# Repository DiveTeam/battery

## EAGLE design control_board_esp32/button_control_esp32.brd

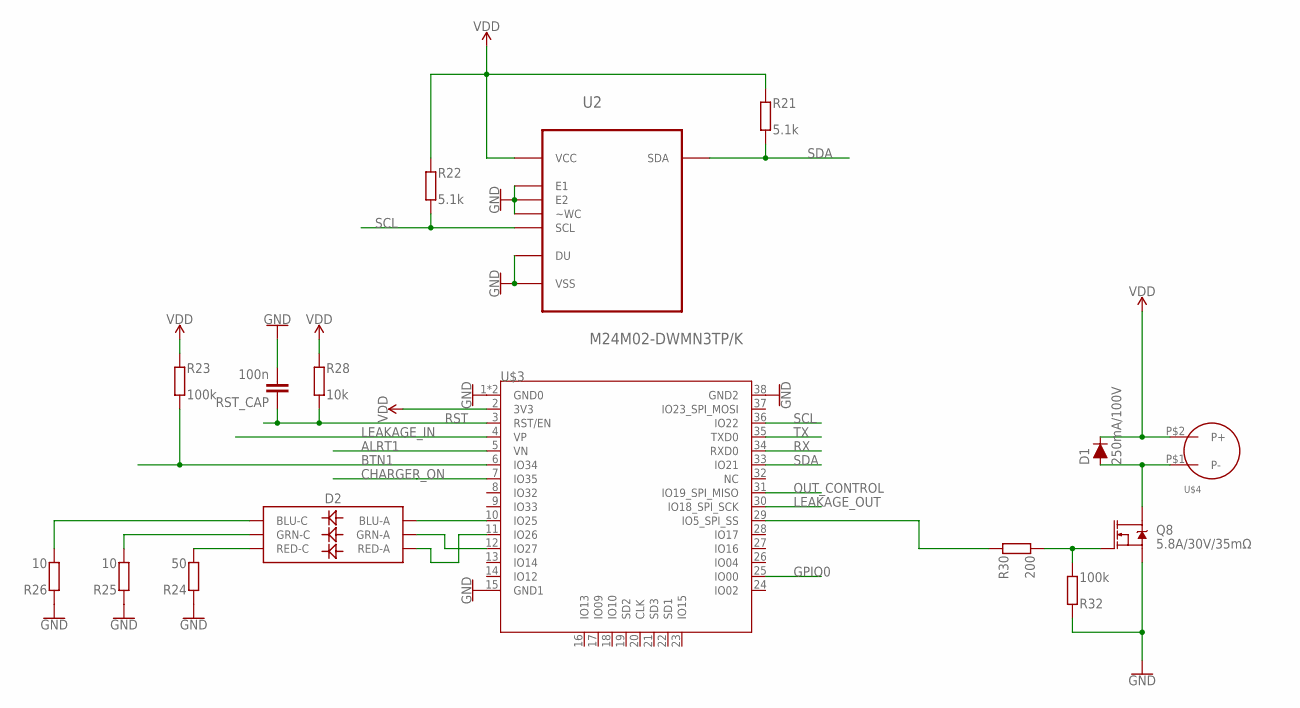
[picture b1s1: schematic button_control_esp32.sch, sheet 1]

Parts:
D1: 250mA/100V; SOD-323
D2: LED-RGBNO_IC; LED-TRICOLOR-5050
Q8: 5.8A/30V/35mΩ; SOT23-3
R21, R22: 5.1k; R0603
R23, R32: 100k; R0603
R24: 50; R0603
R25, R26: 10; R0603
R28: 10k; R0603
R30: 200; R0603
RST_CAP: 100n; C0603
U2: M24M02-DWMN3TP/K; SOIC127P600X175-8N
U$3: ESP32; TTGO_ESP32
U$4: VIBRO

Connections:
ALRT1: U$3.5 (VN); also elsewhere on the board
BTN1: R23.1, U$3.6 (IO34); also elsewhere on the board
CHARGER_ON: U$3.7 (IO35); also elsewhere on the board
GND: Q8.2 (S), R24.2, R25.2, R26.2, R32.2, RST_CAP.2, U2.1 (DU), U2.2 (E1), U2.3 (E2), U2.4 (VSS), U2.7 (~WC), U$3.1 (GND0), U$3.15 (GND1), U$3.38 (GND2), U$3.P$1 (GND0); also elsewhere on the board
GPIO0: U$3.25 (IO00); also elsewhere on the board
LEAKAGE_IN: U$3.4 (VP); also elsewhere on the board
LEAKAGE_OUT: U$3.30 (IO18_SPI_SCK); also elsewhere on the board
unnamed: D2.3 (BLU-A), U$3.10 (IO25)
unnamed: D2.1 (GRN-A), U$3.12 (IO27)
unnamed: D2.2 (RED-A), U$3.11 (IO26)
unnamed: Q8.1 (G), R30.1, R32.1
unnamed: R30.2, U$3.29 (IO5_SPI_SS)
unnamed: D2.4 (BLU-C), R26.1
unnamed: D2.6 (GRN-C), R25.1
unnamed: D2.5 (RED-C), R24.1
unnamed: D1.A, Q8.3 (D), U$4.P$1 (P-)
OUT_CONTROL: U$3.31 (IO19_SPI_MISO); also elsewhere on the board
RST: R28.1, RST_CAP.1, U$3.3 (RST/EN); also elsewhere on the board
RX: U$3.34 (RXD0); also elsewhere on the board
SCL: R22.1, U2.6 (SCL), U$3.36 (IO22); also elsewhere on the board
SDA: R21.1, U2.5 (SDA), U$3.33 (IO21); also elsewhere on the board
TX: U$3.35 (TXD0); also elsewhere on the board
VDD: D1.C, R21.2, R22.2, R23.2, R28.2, U2.8 (VCC), U$3.2 (3V3), U$4.P$2 (P+); also elsewhere on the board

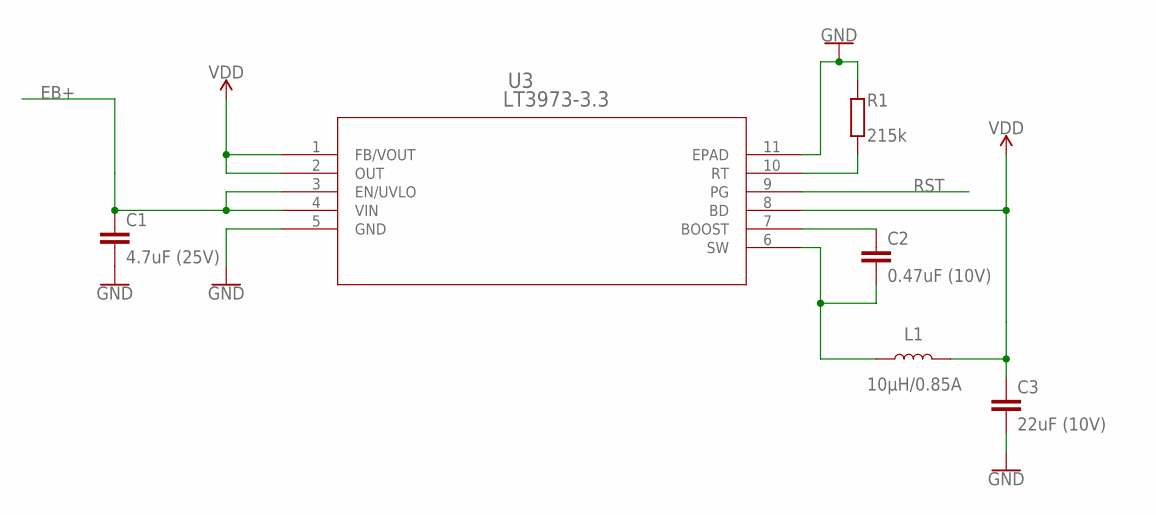
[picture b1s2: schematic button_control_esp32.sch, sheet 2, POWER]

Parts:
C1: 4.7uF (25V); C1206
C2: 0.47uF (10V); C0603K
C3: 22uF (10V); C1206
L1: 10µH/0.85A; INDUCTOR_4.7UH
R1: 215k; R0603
U3: LT3973-3.3; DFN-10_DD

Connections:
BOOST: C2.1, U3.7 (BOOST)
EB+: C1.1, U3.3 (EN/UVLO), U3.4 (VIN); also elsewhere on the board
GND: C1.2, C3.2, R1.2, U3.5 (GND), U3.11 (EPAD); also elsewhere on the board
RST: U3.9 (PG); also elsewhere on the board
RT: R1.1, U3.10 (RT)
SW: C2.2, L1.P$1 (1), U3.6 (SW)
VDD: C3.1, L1.P$2 (2), U3.1 (FB/VOUT), U3.2 (OUT), U3.8 (BD); also elsewhere on the board

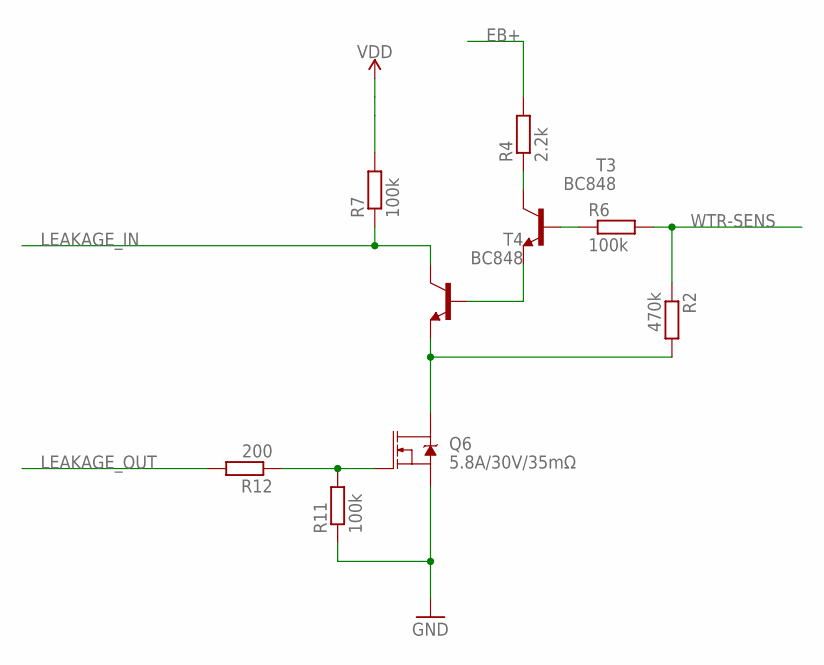
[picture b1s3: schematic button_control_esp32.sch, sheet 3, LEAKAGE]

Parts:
Q6: 5.8A/30V/35mΩ; SOT23-3
R2: 470k; R0603
R4: 2.2k; R0603
R6, R7, R11: 100k; R0603
R12: 200; R0603
T3, T4: BC848; SOT23

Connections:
EB+: R4.2; also elsewhere on the board
GND: Q6.2 (S), R11.1; also elsewhere on the board
LEAKAGE_IN: R7.1, T4.3 (C); also elsewhere on the board
LEAKAGE_OUT: R12.2; also elsewhere on the board
unnamed: T3.2 (E), T4.1 (B)
unnamed: R6.1, T3.1 (B)
unnamed: Q6.3 (D), R2.2, T4.2 (E)
VDD: R7.2; also elsewhere on the board
WTR-SENS: R2.1, R6.2; also elsewhere on the board
WTR_MEASURE_ON1: Q6.1 (G), R11.2, R12.1
WTR_MEASURE_PULLUP1: R4.1, T3.3 (C)

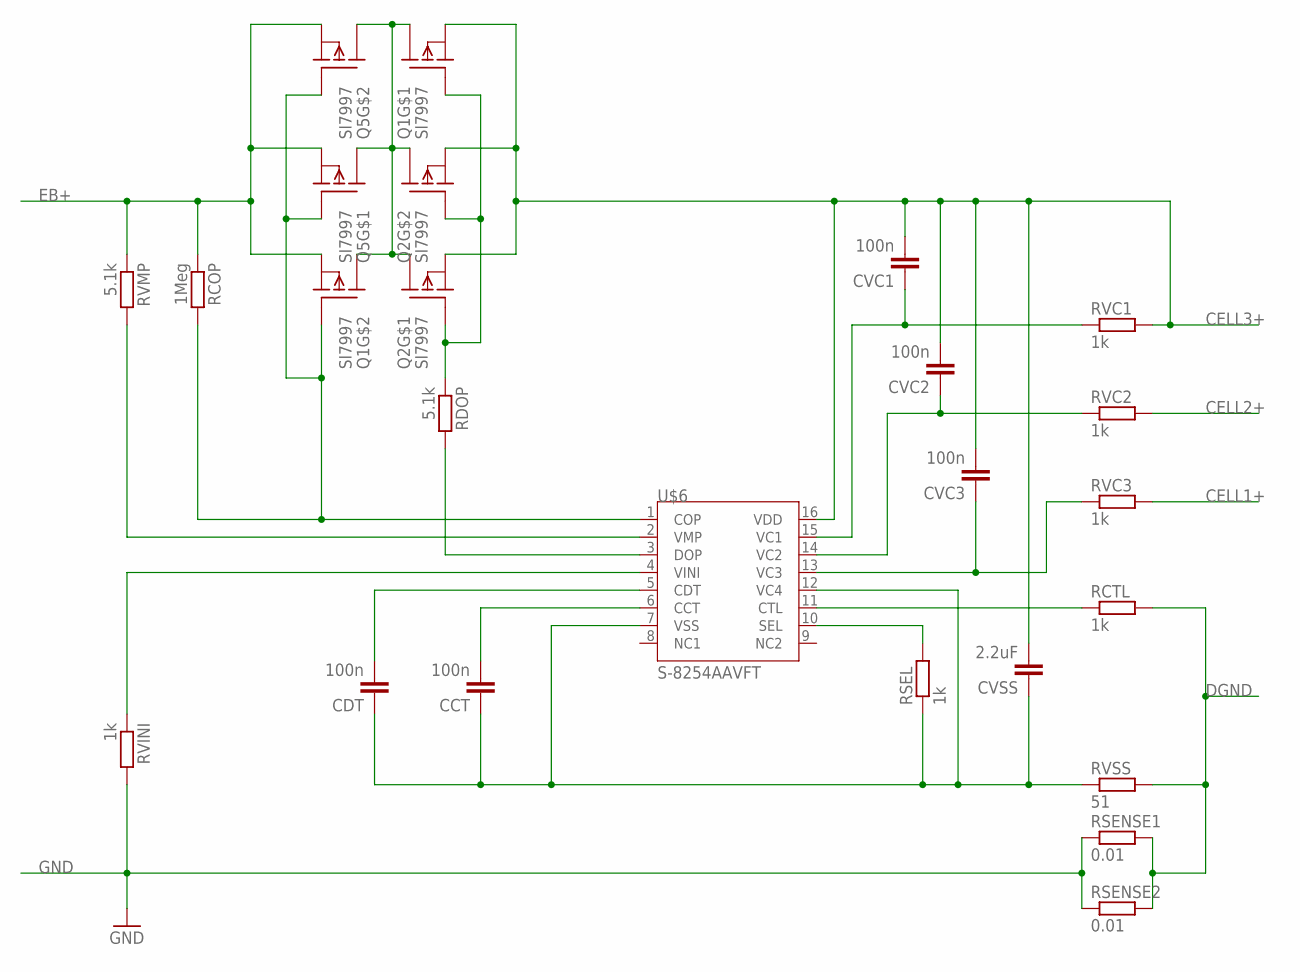
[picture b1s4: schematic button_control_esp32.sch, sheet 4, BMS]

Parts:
CCT: 100n; C0603
CDT: 100n; C0603
CVC1, CVC2, CVC3: 100n; C0603
CVSS: 2.2uF; C0805
Q1, Q2, Q5: SI7997; POWERPAK
RCOP: 1Meg; R0603
RCTL: 1k; R0603
RDOP: 5.1k; R0603
RSEL: 1k; R0603
RSENSE1, RSENSE2: 0.01; R2512
RVC1, RVC2, RVC3: 1k; R0603
RVINI: 1k; R0603
RVMP: 5.1k; R0603
RVSS: 51; R0603
U$6: S-8254AAVFT; TSSOP-16

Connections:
CELL1+: RVC3.2; also elsewhere on the board
CELL2+: RVC2.2; also elsewhere on the board
CELL3+: CVC1.2, CVC2.2, CVC3.2, CVSS.2, Q1.1 (S), Q2.1 (S), Q2.3 (S), RVC1.2, U$6.16 (VDD); also elsewhere on the board
DGND: RCTL.2, RSENSE1.2, RSENSE2.2, RVSS.2; also elsewhere on the board
EB+: Q1.3 (S), Q5.1 (S), Q5.3 (S), RCOP.1, RVMP.1; also elsewhere on the board
GND: RSENSE1.1, RSENSE2.1, RVINI.2; also elsewhere on the board
unnamed: RDOP.2, U$6.3 (DOP)
unnamed: Q1.4 (G), Q5.2 (G), Q5.4 (G), RCOP.2, U$6.1 (COP)
unnamed: Q1.2 (G), Q2.2 (G), Q2.4 (G), RDOP.1
unnamed: RVMP.2, U$6.2 (VMP)
unnamed: RSEL.2, U$6.10 (SEL)
unnamed: RVINI.1, U$6.4 (VINI)
unnamed: CDT.2, U$6.5 (CDT)
unnamed: CCT.2, U$6.6 (CCT)
unnamed: CCT.1, CDT.1, CVSS.1, RSEL.1, RVSS.1, U$6.7 (VSS), U$6.12 (VC4)
unnamed: RCTL.1, U$6.11 (CTL)
unnamed: Q1.5 (D), Q1.5_6 (D), Q1.6 (D), Q1.7 (D), Q1.7_8 (D), Q1.8 (D), Q2.5 (D), Q2.5_6 (D), Q2.6 (D), Q2.7 (D), Q2.7_8 (D), Q2.8 (D), Q5.5 (D), Q5.5_6 (D), Q5.6 (D), Q5.7 (D), Q5.7_8 (D), Q5.8 (D)
unnamed: CVC3.1, RVC3.1, U$6.13 (VC3)
unnamed: CVC2.1, RVC2.1, U$6.14 (VC2)
unnamed: CVC1.1, RVC1.1, U$6.15 (VC1)

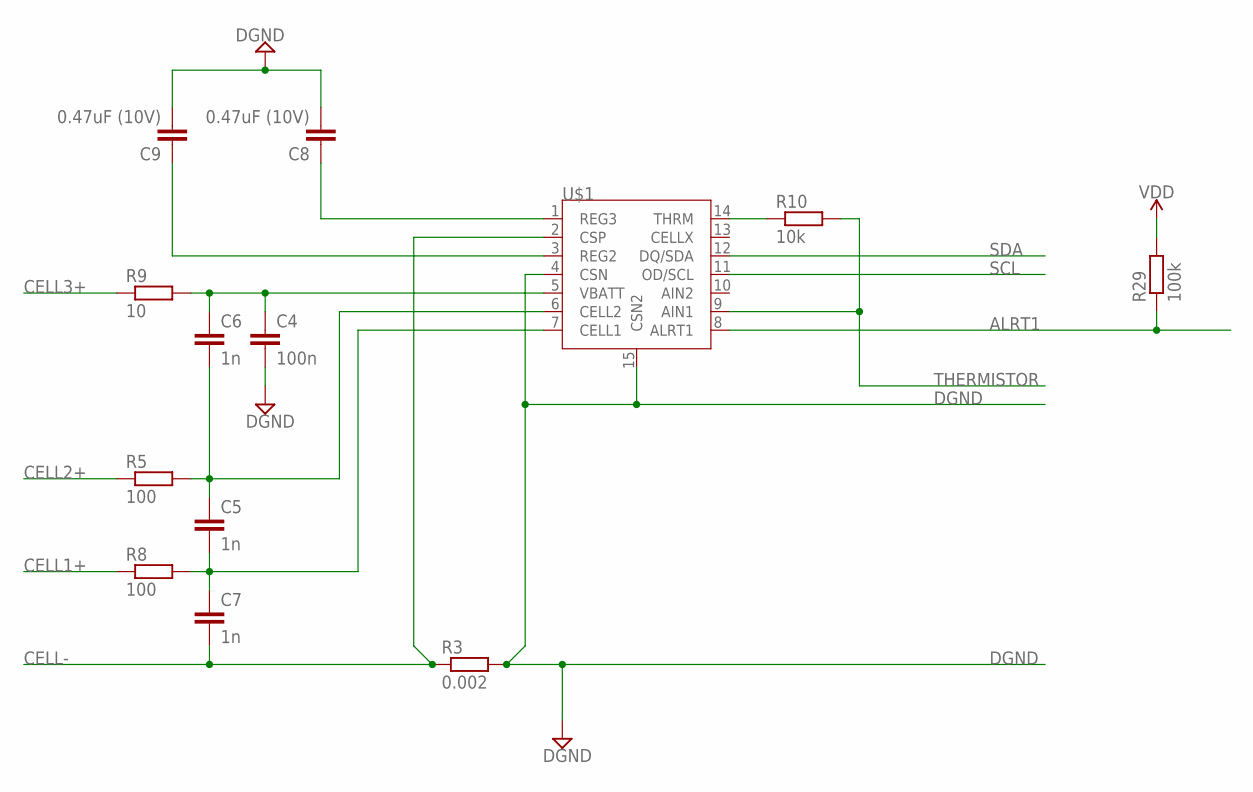
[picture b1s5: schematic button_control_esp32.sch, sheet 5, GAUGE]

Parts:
C4: 100n; C0603
C5, C6, C7: 1n; C0603
C8, C9: 0.47uF (10V); C0603K
R3: 0.002; R2512
R5, R8: 100; R0805
R9: 10; R0603
R10: 10k; R0603
R29: 100k; R0603
U$1: MAX17205G; SON40P300X300X80-15N230X170

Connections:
ALRT1: R29.1, U$1.8 (ALRT1); also elsewhere on the board
CELL1+: R8.1; also elsewhere on the board
CELL2+: R5.1; also elsewhere on the board
CELL3+: R9.1; also elsewhere on the board
CELL-: C7.2, R3.1, U$1.2 (CSP); also elsewhere on the board
DGND: C4.2, C8.2, C9.2, R3.2, U$1.4 (CSN), U$1.15 (CSN2); also elsewhere on the board
unnamed: C4.1, C6.1, R9.2, U$1.5 (VBATT)
unnamed: C5.1, C6.2, R5.2, U$1.6 (CELL2)
unnamed: C5.2, C7.1, R8.2, U$1.7 (CELL1)
unnamed: R10.1, U$1.14 (THRM)
unnamed: C8.1, U$1.1 (REG3)
unnamed: C9.1, U$1.3 (REG2)
SCL: U$1.11 (OD/SCL); also elsewhere on the board
SDA: U$1.12 (DQ/SDA); also elsewhere on the board
THERMISTOR: R10.2, U$1.9 (AIN1); also elsewhere on the board
VDD: R29.2; also elsewhere on the board

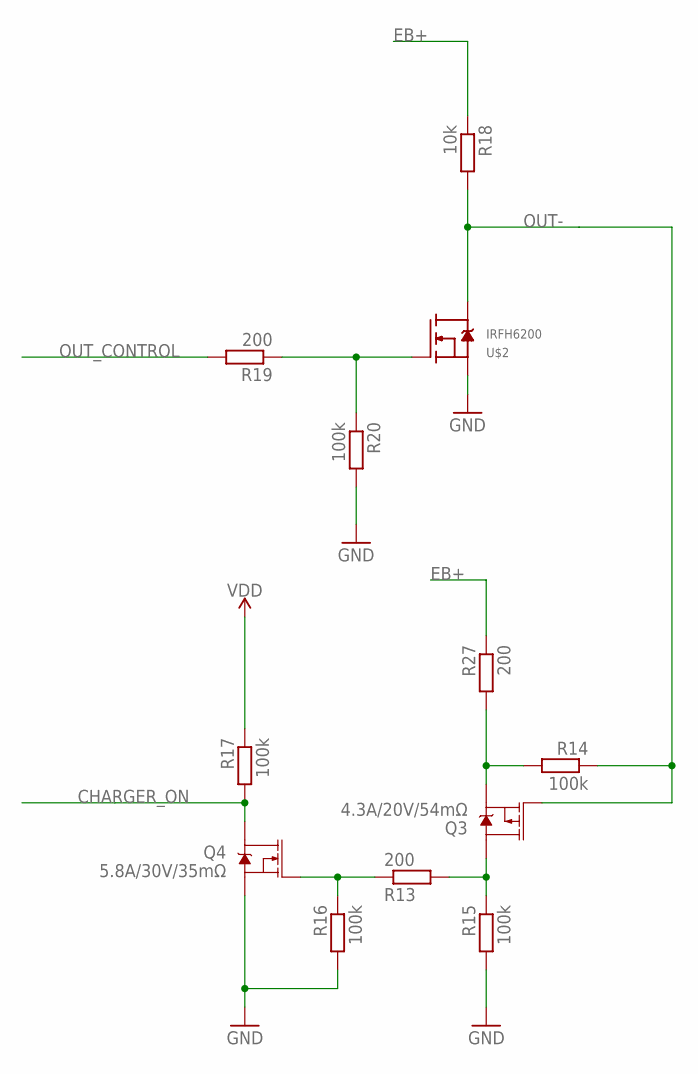
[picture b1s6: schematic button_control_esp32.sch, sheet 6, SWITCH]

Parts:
Q3: 4.3A/20V/54mΩ; SOT23-3
Q4: 5.8A/30V/35mΩ; SOT23-3
R13, R19, R27: 200; R0603
R14, R15, R16, R17, R20: 100k; R0603
R18: 10k; R0603
U$2: IRFH6200; PQFN

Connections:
CHARGER_ON: Q4.3 (D), R17.2; also elsewhere on the board
EB+: R18.1, R27.1; also elsewhere on the board
GND: Q4.2 (S), R15.2, R16.2, R20.2, U$2.1 (S), U$2.2 (S), U$2.3 (S); also elsewhere on the board
unnamed: Q3.3 (D), R13.2, R15.1
unnamed: Q4.1 (G), R13.1, R16.1
unnamed: Q3.2 (S), R14.2, R27.2
OUT-: Q3.1 (G), R14.1, R18.2, U$2.5 (D), U$2.6 (D), U$2.7 (D), U$2.8 (D), U$2.9 (D); also elsewhere on the board
OUT_BASE: R19.1, R20.1, U$2.4 (G)
OUT_CONTROL: R19.2; also elsewhere on the board
VDD: R17.1; also elsewhere on the board

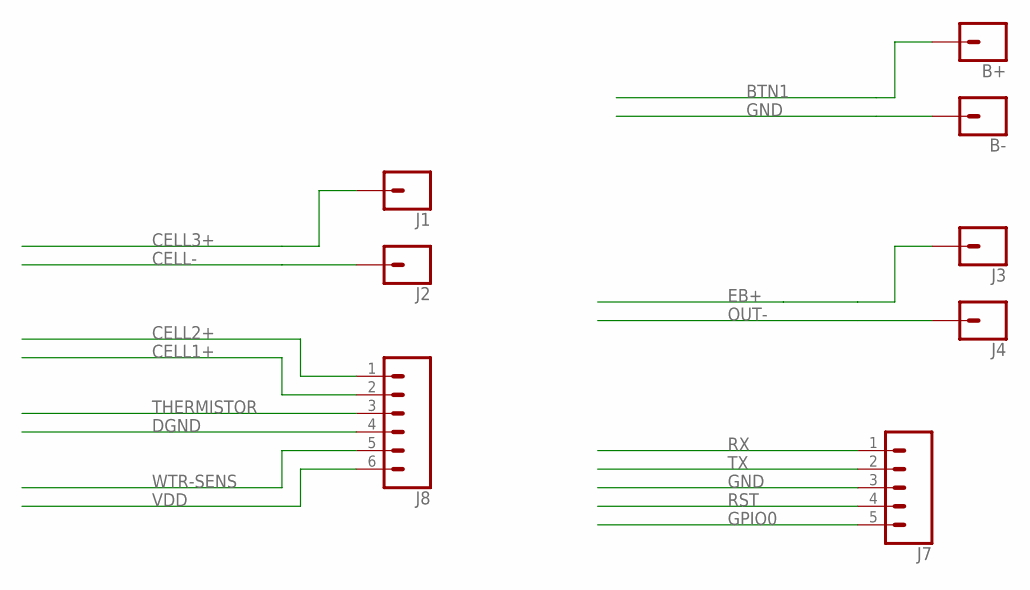
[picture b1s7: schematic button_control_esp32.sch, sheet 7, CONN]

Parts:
B+: CONN_01; 1X01
B-: CONN_01; 1X01
J1, J2, J3, J4: CONN_01PTH_2MM; 1X01_2MM
J7: CONN_051.27MM; 1X05_1.27MM
J8: CONN_061.27MM; 1X06_1.27MM

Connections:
BTN1: B+.1; also elsewhere on the board
CELL1+: J8.2; also elsewhere on the board
CELL2+: J8.1; also elsewhere on the board
CELL3+: J1.1; also elsewhere on the board
CELL-: J2.1; also elsewhere on the board
DGND: J8.4; also elsewhere on the board
EB+: J3.1; also elsewhere on the board
GND: B-.1, J7.3; also elsewhere on the board
GPIO0: J7.5; also elsewhere on the board
OUT-: J4.1; also elsewhere on the board
RST: J7.4; also elsewhere on the board
RX: J7.1; also elsewhere on the board
THERMISTOR: J8.3; also elsewhere on the board
TX: J7.2; also elsewhere on the board
VDD: J8.6; also elsewhere on the board
WTR-SENS: J8.5; also elsewhere on the board

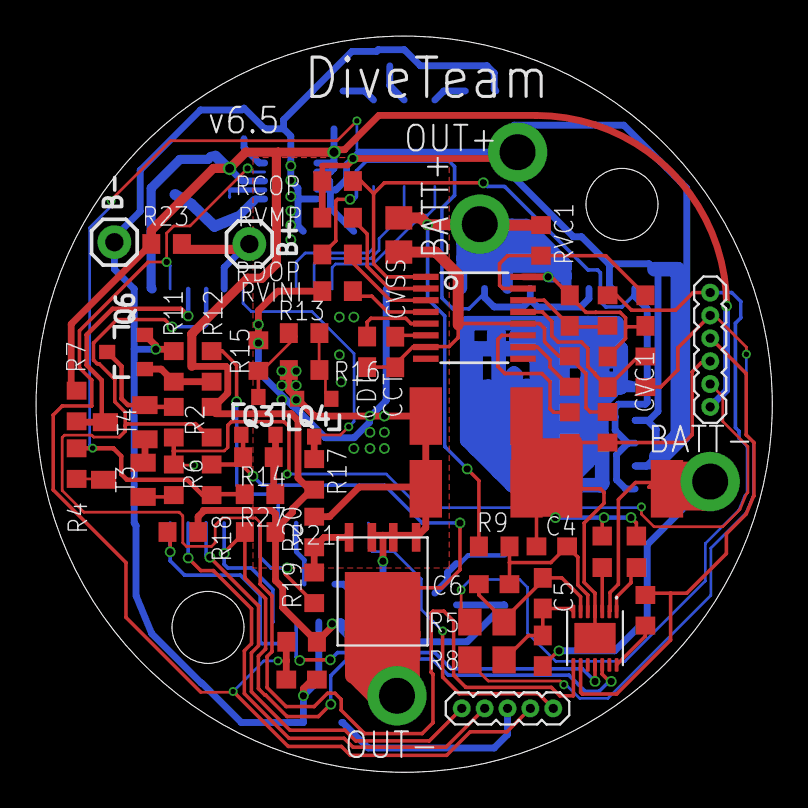
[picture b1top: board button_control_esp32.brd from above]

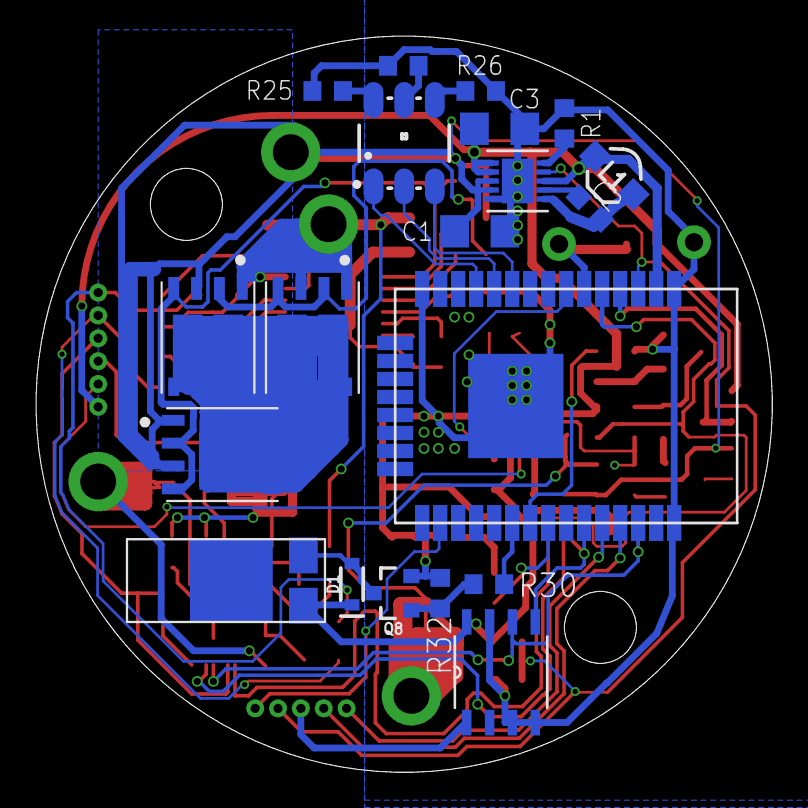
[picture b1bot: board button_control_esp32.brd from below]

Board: 2 copper layers, 40.9 x 40.9 mm, 86 parts (22 on the bottom side), 64 nets.

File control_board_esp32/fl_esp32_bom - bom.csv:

Qty,Designator,Footprint,Comment,LCSC Part#
1,R3,R2010,0.002,C76234
2,"RSENSE1, RSENSE2",R2512,0.01,C76242
3,"C2, C8, C9",C0603K,0.47uF (10V),
3,"R9, R25, R26",R0603,10,
1,R30,R0603,100,
2,"R5, R8",R0805,100,
11,"R6, R7, R11, R14, R15, R16, R17, R20, R23, R29, R32",R0603,100k,
7,"C4, CCT, CDT, CVC1, CVC2, CVC3, RST_CAP",C0603,100n,
3,"R10, R18, R28",R0603,10k,
1,L1,INDUCTOR_4.7UH,10µH/0.85A,
1,RCOP,R0603,1Meg,
6,"RCTL, RSEL, RVC1, RVC2, RVC3, RVINI",R0603,1k,
3,"C5, C6, C7",C0603,1n,
1,R4,R0603,2.2k,
1,CVSS,C0805,2.2uF,
4,"R12, R13, R19, R27",R0603,200,
1,R1,R0603,215k,
1,C3,C1206,22uF (10V),
1,D1,SOD-323,250mA/100V,
1,Q3,SOT23-3,4.3A/20V/54mΩ,C169763
1,C1,C1206,4.7uF (25V),
1,R2,R0603,470k,
4,"R21, R22, RDOP, RVMP",R0603,5.1k,
3,"Q4, Q6, Q8",SOT23-3,5.8A/30V/35mΩ,C30010
2,"R24, R31",R0603,50,
1,RVSS,R0603,51,
2,"T3, T4",SOT23,BC848,C8576
1,U$3,TTGO_ESP32,ESP32,
1,U$2,PQFN,IRFH6200,C151522
1,U3,DFN-10_DD,LT3973-3.3,
1,U2,SOIC127P600X175-8N,M24M02-DWMN3TP/K,
1,U$1,SON40P300X300X80-15N230X170,MAX17205G,C401140
1,U$6,TSSOP-16,S-8254A,
3,"Q1, Q2, Q5",POWERPAK,SI7997,

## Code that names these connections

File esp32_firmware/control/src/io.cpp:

#include "io.h"
#include "globals.h"
#include "soc/ledc_reg.h"
#include "soc/ledc_struct.h"
// #include "max1720x.h"
// #include <Arduino.h>
// #include <Wire.h>
#include <extEEPROM.h>


#define VIBRO_PIN 5

//this is just to make it look pretty and have some spare bytes. try not exceed 29-30 bytes to avoid buffer tearing (Arduino cant send more thatn 32 bytes at once)
#define LOG_RECORD_SIZE 32
#define LOG_FIRST_RECORD_OFFSET 256 //let's leave first 256 bytes (page) for other variables
#define LOGS_FIT_TO_EEPROM 7800
#define EEPROM_ADDR_POSITION_COUNTER 0


extEEPROM myEEPROM(kbits_2048, 1, 256); //single EEPROM, 256 bytes page

void setup_led(){
  ledcSetup(0, 5000, 8); //setting up PWM (3 channels) at 5Hz frequency with 8-bit resolution
  ledcSetup(1, 5000, 8);
  ledcSetup(2, 5000, 8);
  ledcAttachPin(26, 0);//RED
  ledcAttachPin(25, 1);//GREEN
  ledcAttachPin(27, 2);//BLUE
  ledcWrite(0, 255);
  ledcWrite(1, 255);
  ledcWrite(2, 255);
}


void IRAM_ATTR button_pressed_isr(){
  wanna_turn_off = 1;
  pinMode(VIBRO_PIN, OUTPUT);
  digitalWrite(VIBRO_PIN, 1);
  //avoid ANYTHING that could potentially be not in RAM. Any functions are bad!
}

void set_LED(uint8_t R, uint8_t G, uint8_t B){
  ledcWrite(0, R);
  ledcWrite(1, G);
  ledcWrite(2, B);
}

void setup_io(){
  //CHARGER_ON -> IO35. aka RTC_GPIO_5. has external 100k pullup to VDD
  //BUTTON -> IO34. aka RTC_GPIO_4. has external 100k pullup to VDD
  //ALRT1 -> IO39 (SVN). aka RTC_GPIO_3. has external 100k pullup to VDD. Alert from BMS
  //LEAKAGE_IN -> IO36 (SVP). aka RTC_GPIO0. has external 100k pullup to VDD
  //OUT_CONTROL -> IO19
  //LEAKAGE_OUT -> IO18
  //VIBRO -> IO5
  // pinMode(VIBRO_PIN, OUTPUT);
  pinMode(18, OUTPUT);
  pinMode(19, OUTPUT);
  pinMode(34, INPUT);
  pinMode(35, INPUT);
  pinMode(36, INPUT);
  pinMode(39, INPUT);

  ledcSetup(3, 5000, 8); //setting up PWM
  ledcAttachPin(VIBRO_PIN, 3);//VIBRO
  ledcWrite(3, 255);
}

void setup_eeprom(){
  byte i2cStat = myEEPROM.begin(extEEPROM::twiClock400kHz);
  if ( i2cStat != 0 ) {
    Serial.println("Unable to start I2C communication");
  }
}

void setup_bms(){
  gauge.writeReg(0x00, 0x0000);		//clear status register
}

uint32_t get_eeprom_offset(uint32_t log_id){
  uint32_t result = ((log_id % LOGS_FIT_TO_EEPROM) * LOG_RECORD_SIZE) + LOG_FIRST_RECORD_OFFSET;
  return result;
}

uint32_t get_log_position(){
  byte readData[4];
  byte i2cStat = myEEPROM.read(EEPROM_ADDR_POSITION_COUNTER, readData, 4);

  if ( i2cStat != 0 ) {
    if ( i2cStat == EEPROM_ADDR_ERR) {
      Serial.println("Error reading data - bad address");
    }
    else {
      Serial.println("Error reading data - I2C error");
    }
  }else{
    uint32_t log_position =  ((uint32_t)readData[3] << 24) + ((uint32_t)readData[2] << 16) + ((uint32_t)readData[1] << 8) + (uint32_t)readData[0];
    return log_position;
  }
  return 0;
}

void IRAM_ATTR read_log_record(uint32_t id, log_record &record_to_read){
  // Serial.print("Offset: ");
  // Serial.println(get_eeprom_offset(id));

  byte* p = ( byte*)( void*)&record_to_read;
  myEEPROM.read(get_eeprom_offset(id), p, sizeof(log_record));
  // Serial.print("Record ID: ");
  // Serial.println(record_to_read.record_id);
}

uint32_t make_log_record(){
  //once a minute + at the start
  if(millis_since_start - last_record_saved_at >= 60000 || last_record_saved_at == 0){
    Serial.print("Making log record ");

    uint32_t log_position = get_log_position();
    current_state.record_id = log_position;
    byte* p = ( byte*)( void*)&current_state;
    Serial.print(log_position + 1);
    Serial.print(" with offset ");
    Serial.println(get_eeprom_offset(log_position + 1));

    // Serial.print("Writing DATA: ");
    // for(uint8_t i=0;i<26;i++){
    //   Serial.println(p[i], HEX);
    // }


    byte i2cStat = myEEPROM.write(get_eeprom_offset(log_position + 1), p, sizeof(current_state));
    if ( i2cStat == 0 ){
      delay(10); //10 ms delay to complete write operation.

      // Serial.print("Reading DATA: ");
      // for(uint8_t i=0;i<26;i++){
      //   Serial.println(myEEPROM.read(get_eeprom_offset(log_position)+i), HEX);
      // }

      log_position++;
      byte new_log_position[4];
      new_log_position[0] = log_position & 0xFF;
      new_log_position[1] = (log_position >> 8) & 0xFF;
      new_log_position[2] = (log_position >> 16) & 0xFF;
      new_log_position[3] = (log_position >> 24) & 0xFF;
      i2cStat = myEEPROM.write(EEPROM_ADDR_POSITION_COUNTER, new_log_position, sizeof(new_log_position)); //zero EEPROM address will store position
      // Serial.print("Updating log position to ");
      // Serial.println(log_position);
    }
    last_record_saved_at = millis_since_start;
    return log_position;
  }
  return 0;
}


void turn_on(){
  Serial.println("Turning on");
  while(!digitalRead(34)){}; //skip button pressed
  digitalWrite(19, 1);//turn on output transistor
  digitalWrite(18, 1);//leakage control oN
  
}


void notify_turning_off(){
  for(uint8_t i=0; i<5; i++){
    for(int dutyCycle = 0; dutyCycle < 255; dutyCycle++){   
      ledcWrite(3, dutyCycle);
      delay(1);
    }

    for(int dutyCycle = 255; dutyCycle >=0; dutyCycle--){   
      ledcWrite(3, dutyCycle);
      delay(1);
    }
  }
}

void turn_off(){
  Serial.println("Turning off");
  ledcWrite(0, 0);
  ledcWrite(1, 0);
  ledcWrite(2, 0);
  ledcWrite(3, 0);
  digitalWrite(19, 0);//turn off output transistor
  while(!digitalRead(34)){}; //skip button pressed
  notify_turning_off();
  wanna_turn_off=0;
  // delay(1000);
  digitalWrite(18, 0);//leakage control off
  delay(500);//to let BT turnoff settle down
  esp_deep_sleep_start();
}


bool is_leaking(){
  return(!digitalRead(36));
}

void reset_position_counter(){
  byte zero_array[4]={0,0,0,0}; //reset log counter to 0
  myEEPROM.write(EEPROM_ADDR_POSITION_COUNTER, zero_array, sizeof(zero_array));
}

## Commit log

2020-10-05 Adds main parts
2020-10-05 Adds firmwares
2020-10-06 Adds ReactNative APP

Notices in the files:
parts and their libraries:
SparkFun-LED: Licensing: Creative Commons ShareAlike 4.0 International - https://creativecommons.org/licenses/by-sa/4.0
